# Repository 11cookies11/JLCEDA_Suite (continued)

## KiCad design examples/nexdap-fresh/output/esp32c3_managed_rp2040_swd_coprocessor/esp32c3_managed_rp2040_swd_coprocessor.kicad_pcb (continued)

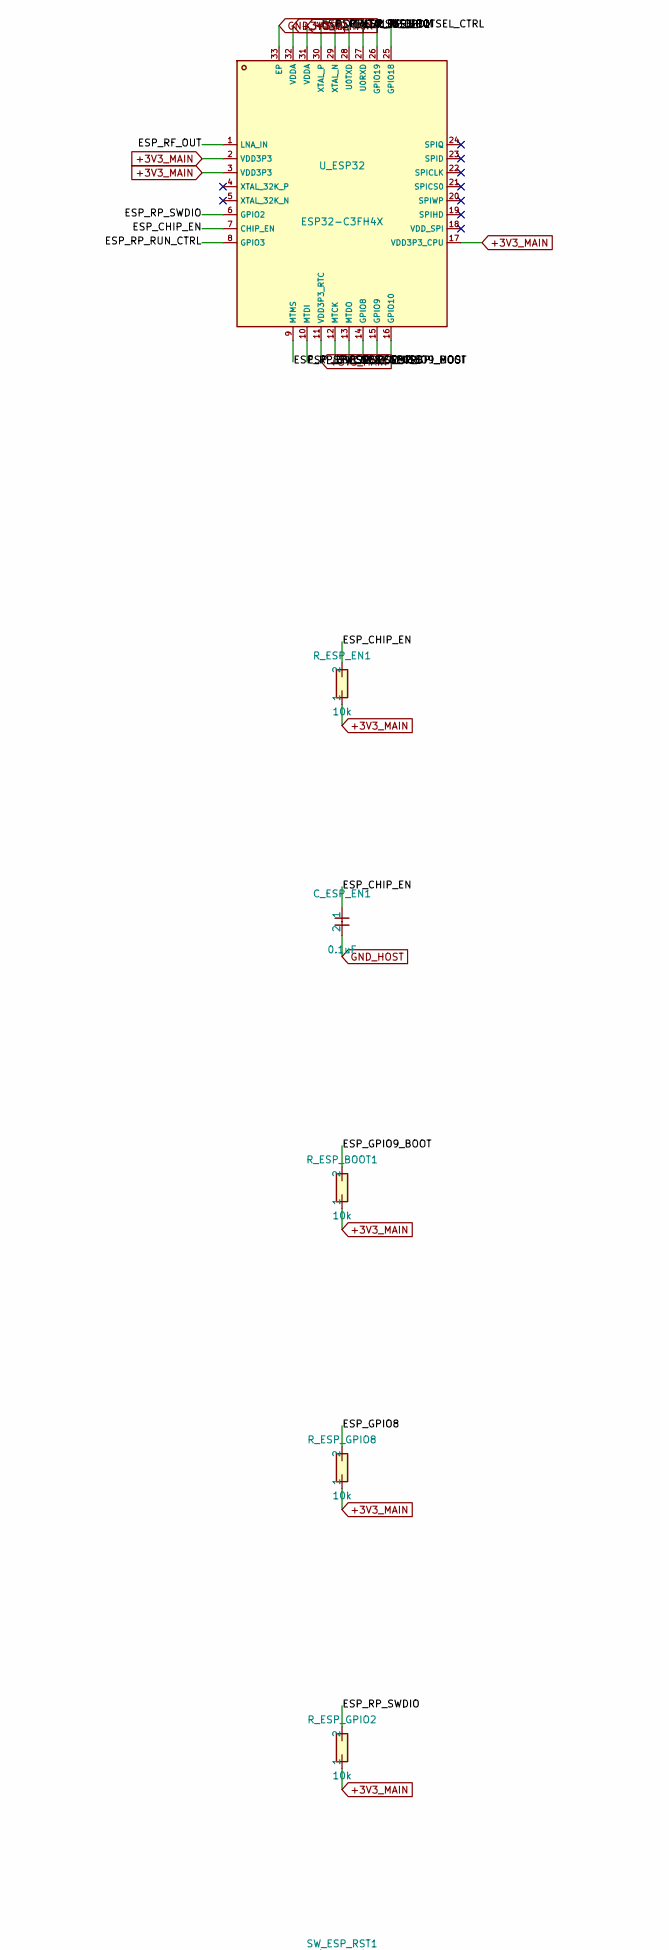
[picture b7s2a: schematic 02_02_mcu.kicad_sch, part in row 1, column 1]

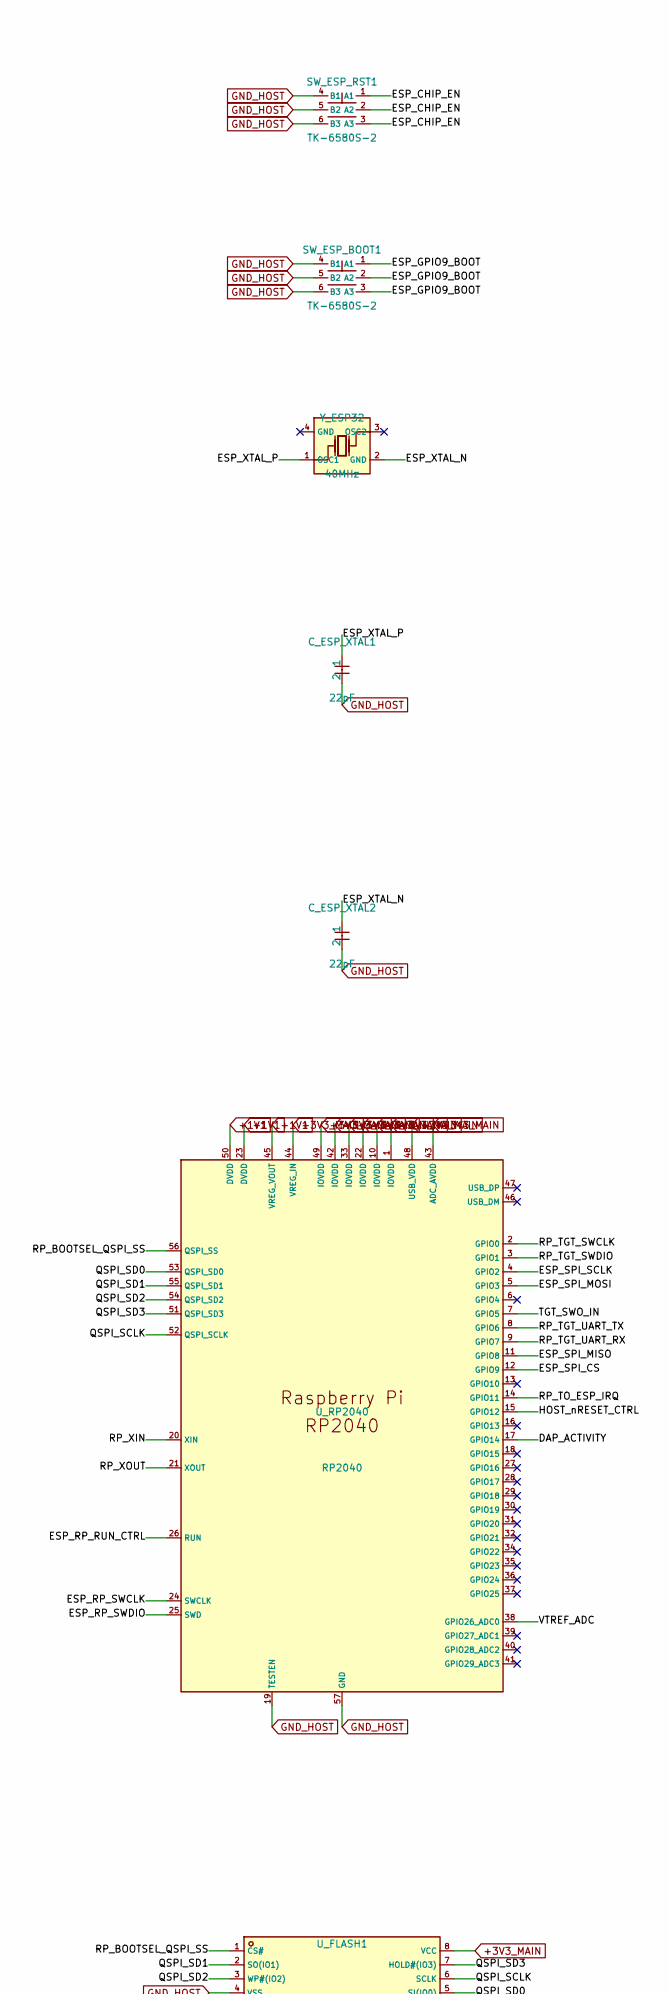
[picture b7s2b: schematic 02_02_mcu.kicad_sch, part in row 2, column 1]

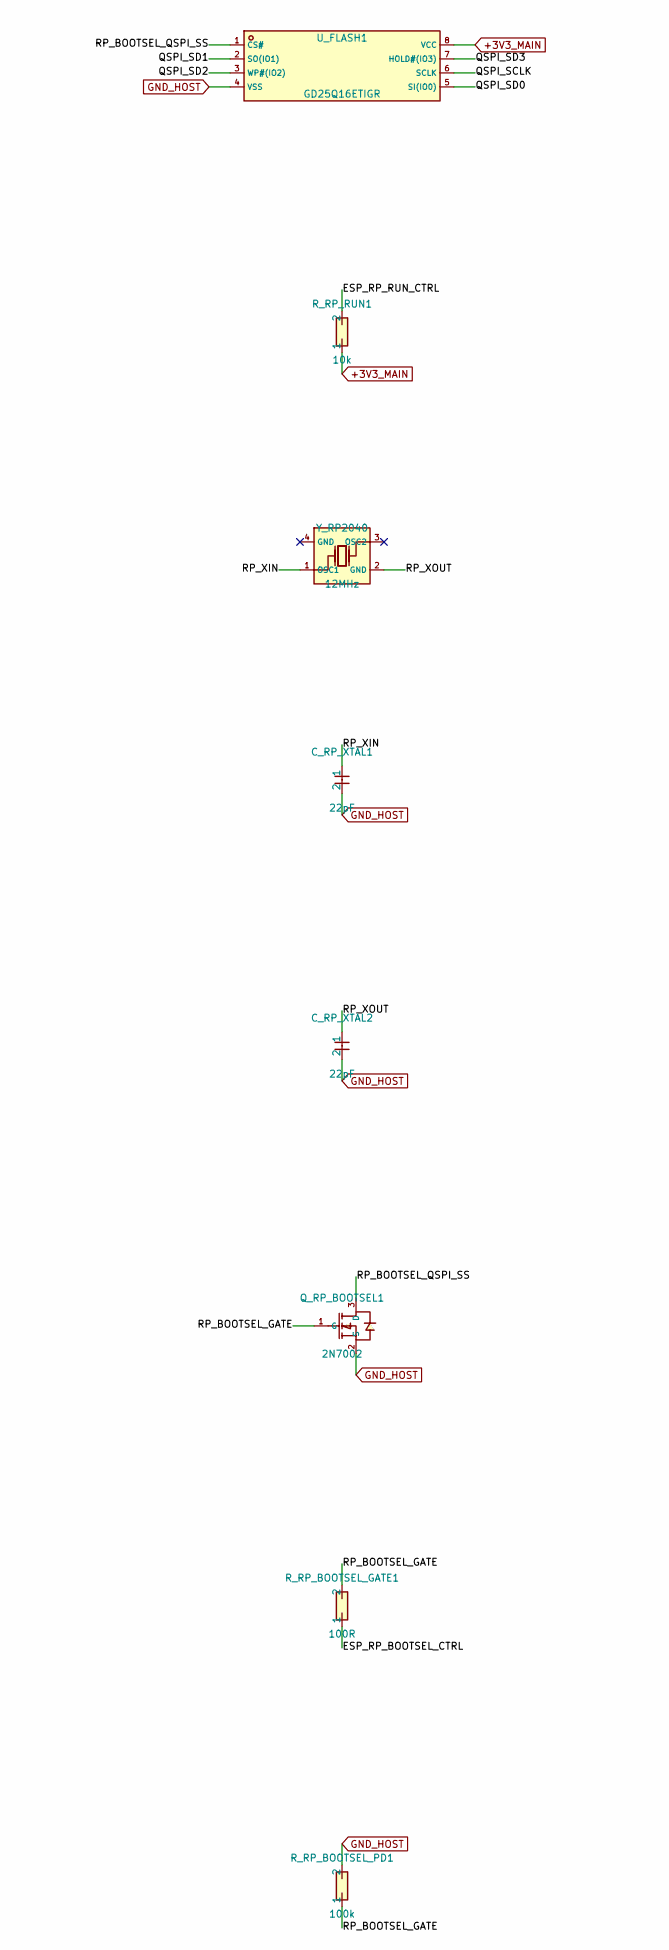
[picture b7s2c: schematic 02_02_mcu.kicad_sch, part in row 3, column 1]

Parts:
C_ESP_EN1: 0.1uF; C0603
C_ESP_XTAL1, C_ESP_XTAL2: 22pF; C0603
C_RP_XTAL1, C_RP_XTAL2: 22pF; C0603
Q_RP_BOOTSEL1: 2N7002; SOT-23-3_L2.9-W1.3-P1.90-LS2.4-BR
R_ESP_BOOT1: 10k; R0603
R_ESP_EN1: 10k; R0603
R_ESP_GPIO2, R_ESP_GPIO8: 10k; R0603
R_RP_BOOTSEL_GATE1: 100R; R0603
R_RP_BOOTSEL_PD1: 100k; R0603
R_RP_RUN1: 10k; R0603
SW_ESP_BOOT1: TK-6580S-2; SW-SMD_TK-6580S-2
SW_ESP_RST1: TK-6580S-2; SW-SMD_TK-6580S-2
U_ESP32: ESP32-C3FH4X; QFN-32_L5.0-W5.0-P0.50-TL-EP3.7
U_FLASH1: GD25Q16ETIGR; SOP-8_L4.9-W3.9-P1.27-LS6.0-BL
U_RP2040: RP2040; LQFN-56_L7.0-W7.0-P0.4-EP
Y_ESP32: 40MHz; CRYSTAL-SMD_4P-L3.2-W2.5-BL
Y_RP2040: 12MHz; CRYSTAL-SMD_4P-L3.2-W2.5-BL

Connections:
+1V1: U_RP2040.23 (DVDD), U_RP2040.45 (VREG_VOUT), U_RP2040.50 (DVDD); also elsewhere on the board
+3V3_MAIN: R_ESP_BOOT1.1, R_ESP_EN1.1, R_ESP_GPIO2.1, R_ESP_GPIO8.1, R_RP_RUN1.1, U_ESP32.2 (VDD3P3), U_ESP32.3 (VDD3P3), U_ESP32.11 (VDD3P3_RTC), U_ESP32.17 (VDD3P3_CPU), U_ESP32.31 (VDDA), U_ESP32.32 (VDDA), U_FLASH1.8 (VCC), U_RP2040.1 (IOVDD), U_RP2040.10 (IOVDD), U_RP2040.22 (IOVDD), U_RP2040.33 (IOVDD), U_RP2040.42 (IOVDD), U_RP2040.43 (ADC_AVDD), U_RP2040.44 (VREG_IN), U_RP2040.48 (USB_VDD), U_RP2040.49 (IOVDD); also elsewhere on the board
/02_mcu/DAP_ACTIVITY: U_RP2040.17 (GPIO14)
/02_mcu/ESP_CHIP_EN: C_ESP_EN1.1, R_ESP_EN1.2, SW_ESP_RST1.1 (A1), SW_ESP_RST1.2 (A2), SW_ESP_RST1.3 (A3), U_ESP32.7 (CHIP_EN)
/02_mcu/ESP_GPIO8: R_ESP_GPIO8.2, U_ESP32.14 (GPIO8)
/02_mcu/ESP_GPIO9_BOOT: R_ESP_BOOT1.2, SW_ESP_BOOT1.1 (A1), SW_ESP_BOOT1.2 (A2), SW_ESP_BOOT1.3 (A3), U_ESP32.15 (GPIO9)
/02_mcu/ESP_RF_OUT: U_ESP32.1 (LNA_IN)
/02_mcu/ESP_RP_BOOTSEL_CTRL: R_RP_BOOTSEL_GATE1.1, U_ESP32.27 (U0RXD)
/02_mcu/ESP_RP_RUN_CTRL: R_RP_RUN1.2, U_ESP32.8 (GPIO3), U_RP2040.26 (RUN)
/02_mcu/ESP_RP_SWCLK: U_ESP32.9 (MTMS), U_RP2040.24 (SWCLK)
/02_mcu/ESP_RP_SWDIO: R_ESP_GPIO2.2, U_ESP32.6 (GPIO2), U_RP2040.25 (SWD)
/02_mcu/ESP_SPI_CS: U_ESP32.12 (MTCK), U_RP2040.12 (GPIO9)
/02_mcu/ESP_SPI_MISO: U_ESP32.13 (MTDO), U_RP2040.11 (GPIO8)
/02_mcu/ESP_SPI_MOSI: U_ESP32.16 (GPIO10), U_RP2040.5 (GPIO3)
/02_mcu/ESP_SPI_SCLK: U_ESP32.10 (MTDI), U_RP2040.4 (GPIO2)
/02_mcu/ESP_XTAL_N: C_ESP_XTAL2.1, U_ESP32.29 (XTAL_N), Y_ESP32.2 (GND)
/02_mcu/ESP_XTAL_P: C_ESP_XTAL1.1, U_ESP32.30 (XTAL_P), Y_ESP32.1 (OSC1)
/02_mcu/HOST_nRESET_CTRL: U_RP2040.15 (GPIO12)
/02_mcu/QSPI_SCLK: U_FLASH1.6 (SCLK), U_RP2040.52 (QSPI_SCLK)
/02_mcu/QSPI_SD0: U_FLASH1.5 (SI(IO0)), U_RP2040.53 (QSPI_SD0)
/02_mcu/QSPI_SD1: U_FLASH1.2 (SO(IO1)), U_RP2040.55 (QSPI_SD1)
/02_mcu/QSPI_SD2: U_FLASH1.3 (WP#(IO2)), U_RP2040.54 (QSPI_SD2)
/02_mcu/QSPI_SD3: U_FLASH1.7 (HOLD#(IO3)), U_RP2040.51 (QSPI_SD3)
/02_mcu/RP_BOOTSEL_GATE: Q_RP_BOOTSEL1.1 (G), R_RP_BOOTSEL_GATE1.2, R_RP_BOOTSEL_PD1.1
/02_mcu/RP_BOOTSEL_QSPI_SS: Q_RP_BOOTSEL1.3 (D), U_FLASH1.1 (CS#), U_RP2040.56 (QSPI_SS)
/02_mcu/RP_TGT_SWCLK: U_RP2040.2 (GPIO0)
/02_mcu/RP_TGT_SWDIO: U_RP2040.3 (GPIO1)
/02_mcu/RP_TGT_UART_RX: U_RP2040.9 (GPIO7)
/02_mcu/RP_TGT_UART_TX: U_RP2040.8 (GPIO6)
/02_mcu/RP_TO_ESP_IRQ: U_ESP32.28 (U0TXD), U_RP2040.14 (GPIO11)
/02_mcu/RP_XIN: C_RP_XTAL1.1, U_RP2040.20 (XIN), Y_RP2040.1 (OSC1)
/02_mcu/RP_XOUT: C_RP_XTAL2.1, U_RP2040.21 (XOUT), Y_RP2040.2 (GND)
/02_mcu/TGT_SWO_IN: U_RP2040.7 (GPIO5)
/02_mcu/USB_DM: U_ESP32.25 (GPIO18)
/02_mcu/USB_DP: U_ESP32.26 (GPIO19)
/02_mcu/VTREF_ADC: U_RP2040.38 (GPIO26_ADC0)
GND_HOST: C_ESP_EN1.2, C_ESP_XTAL1.2, C_ESP_XTAL2.2, C_RP_XTAL1.2, C_RP_XTAL2.2, Q_RP_BOOTSEL1.2 (S), R_RP_BOOTSEL_PD1.2, SW_ESP_BOOT1.4 (B1), SW_ESP_BOOT1.5 (B2), SW_ESP_BOOT1.6 (B3), SW_ESP_RST1.4 (B1), SW_ESP_RST1.5 (B2), SW_ESP_RST1.6 (B3), U_ESP32.33 (EP), U_FLASH1.4 (VSS), U_RP2040.19 (TESTEN), U_RP2040.57 (GND); also elsewhere on the board

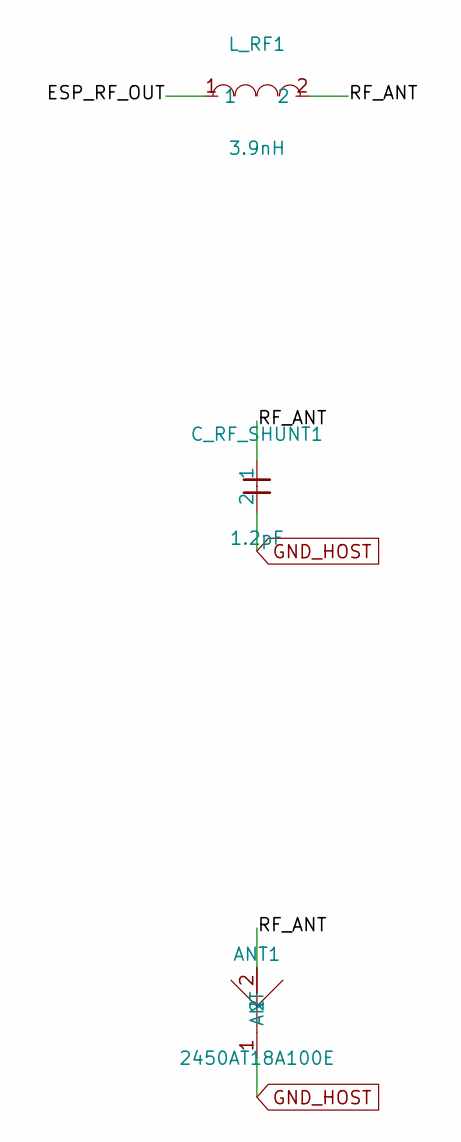
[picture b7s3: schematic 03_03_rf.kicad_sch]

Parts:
ANT1: 2450AT18A100E; ANT-SMD_L3.2-W1.6; MPN 2450AT18A100E; LCSC C89334
C_RF_SHUNT1: 1.2pF; C0603
L_RF1: 3.9nH; IND-SMD_L1.2-W0.7; MPN CS0402-3N9G-S; LCSC C285959

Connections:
/03_rf/ESP_RF_OUT: L_RF1.1
/03_rf/RF_ANT: ANT1.2, C_RF_SHUNT1.1, L_RF1.2
GND_HOST: ANT1.1 (ANT), C_RF_SHUNT1.2; also elsewhere on the board

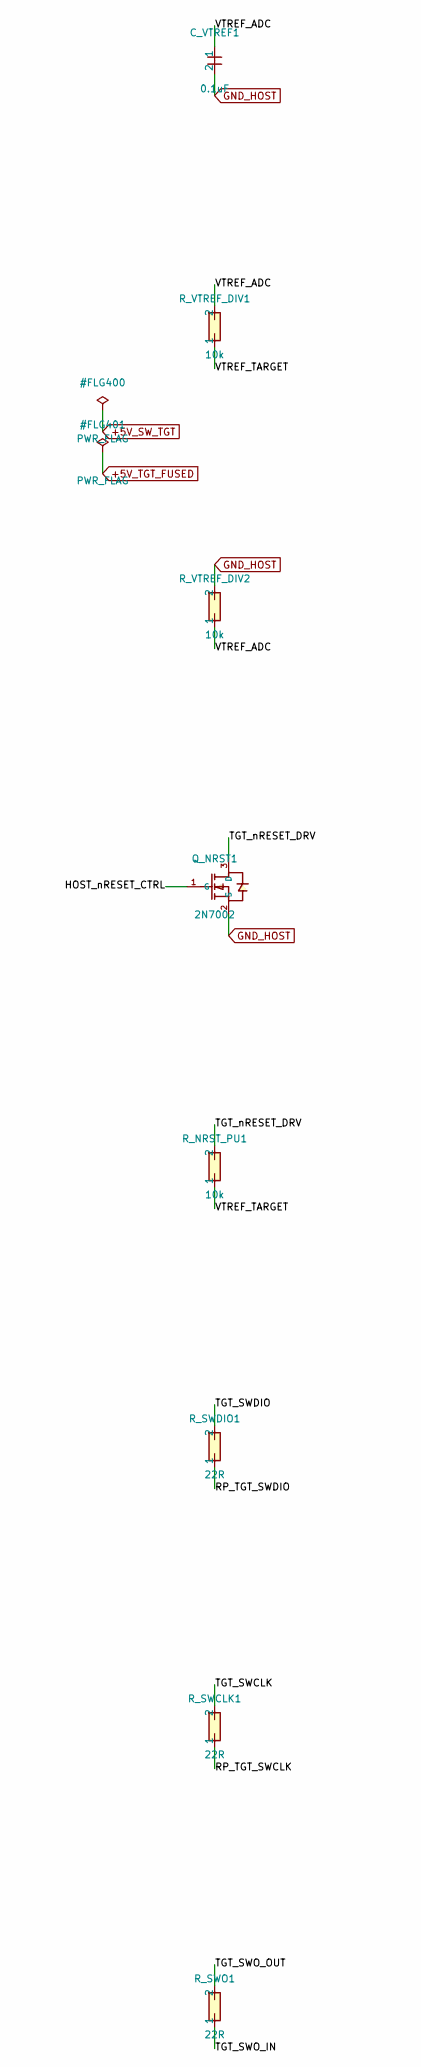
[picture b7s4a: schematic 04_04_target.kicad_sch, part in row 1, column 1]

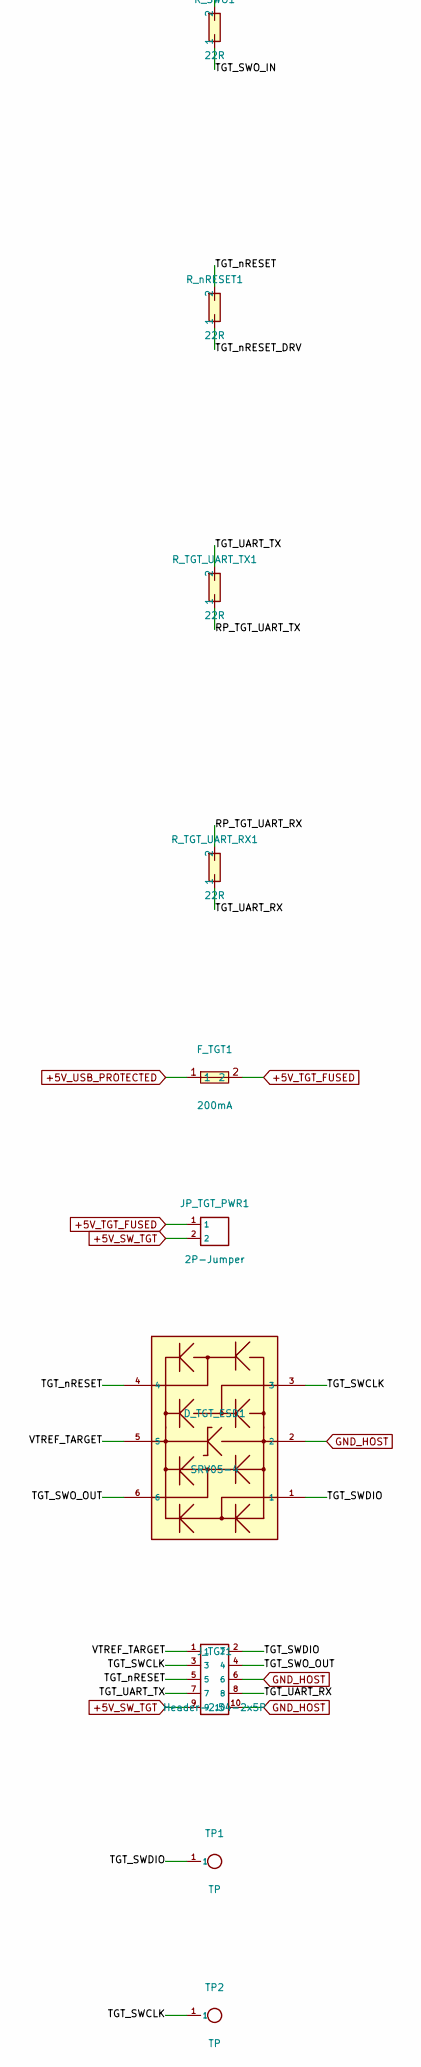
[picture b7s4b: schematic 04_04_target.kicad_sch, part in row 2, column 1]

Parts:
C_VTREF1: 0.1uF; C0603
D_TGT_ESD1: SRV05-4; SOT-23-6_L2.9-W1.6-P0.95-LS2.8-BL
F_TGT1: 200mA; F0805; MPN 0805L020/30XR; LCSC C7472560
JP_TGT_PWR1: 2P-Jumper; HDR-TH_2P-P2.54-V-M
J_TGT1: Header-2.54-2x5P; HDR-TH_10P-P2.54-V-M-2X5
Q_NRST1: 2N7002; SOT-23-3_L2.9-W1.3-P1.90-LS2.4-BR
R_NRST_PU1: 10k; R0603
R_SWCLK1: 22R; R0603
R_SWDIO1: 22R; R0603
R_SWO1: 22R; R0603
R_TGT_UART_RX1: 22R; R0603
R_TGT_UART_TX1: 22R; R0603
R_VTREF_DIV1, R_VTREF_DIV2: 10k; R0603
R_nRESET1: 22R; R0603
TP1, TP2: TP; TP-SMD_1P

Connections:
+5V_SW_TGT: JP_TGT_PWR1.2, J_TGT1.9; also elsewhere on the board
+5V_TGT_FUSED: F_TGT1.2, JP_TGT_PWR1.1
+5V_USB_PROTECTED: F_TGT1.1; also elsewhere on the board
/04_target/HOST_nRESET_CTRL: Q_NRST1.1 (G)
/04_target/RP_TGT_SWCLK: R_SWCLK1.1
/04_target/RP_TGT_SWDIO: R_SWDIO1.1
/04_target/RP_TGT_UART_RX: R_TGT_UART_RX1.2
/04_target/RP_TGT_UART_TX: R_TGT_UART_TX1.1
/04_target/TGT_SWCLK: D_TGT_ESD1.3, J_TGT1.3, R_SWCLK1.2, TP2.1 (1_1)
/04_target/TGT_SWDIO: D_TGT_ESD1.1, J_TGT1.2, R_SWDIO1.2, TP1.1 (1_1)
/04_target/TGT_SWO_IN: R_SWO1.1
/04_target/TGT_SWO_OUT: D_TGT_ESD1.6, J_TGT1.4, R_SWO1.2
/04_target/TGT_UART_RX: J_TGT1.8, R_TGT_UART_RX1.1
/04_target/TGT_UART_TX: J_TGT1.7, R_TGT_UART_TX1.2
/04_target/TGT_nRESET: D_TGT_ESD1.4, J_TGT1.5, R_nRESET1.2
/04_target/TGT_nRESET_DRV: Q_NRST1.3 (D), R_NRST_PU1.2, R_nRESET1.1
/04_target/VTREF_ADC: C_VTREF1.1, R_VTREF_DIV1.2, R_VTREF_DIV2.1
/04_target/VTREF_TARGET: D_TGT_ESD1.5, J_TGT1.1, R_NRST_PU1.1, R_VTREF_DIV1.1
GND_HOST: C_VTREF1.2, D_TGT_ESD1.2, J_TGT1.6, J_TGT1.10, Q_NRST1.2 (S), R_VTREF_DIV2.2; also elsewhere on the board

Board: 2 copper layers, 68 parts (0 on the bottom side), 49 nets, no tracks yet.

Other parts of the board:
LED_DAP1: Blue; LED0603-RD
LED_PWR1: Green; LED0603-RD
LED_TGT1: Red; LED0603-RD
R_LED_DAP1: 330R; R0603
R_LED_PWR1: 330R; R0603
R_LED_TGT1: 330R; R0603

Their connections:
+3V3_MAIN: R_LED_DAP1.1, R_LED_PWR1.1; also elsewhere on the board
+5V_SW_TGT: R_LED_TGT1.1; also elsewhere on the board
/05_indicator/LED_DAP_A: LED_DAP1.2 (+), R_LED_DAP1.2
/05_indicator/LED_PWR_A: LED_PWR1.2 (+), R_LED_PWR1.2
/05_indicator/LED_TGT_K: LED_TGT1.2 (+), R_LED_TGT1.2
GND_HOST: LED_PWR1.1 (-), LED_TGT1.1 (-); also elsewhere on the board

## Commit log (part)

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2026-04-07 docs(repo): define JLCEDA AIAgent foundation
    English summary:
    - replace template README content with project-specific positioning
    - add Where planning files and repository agent guidance
    中文摘要：
    - 将模板 README 替换为项目专用说明
    - 增加 Where 规划文件与仓库级代理约定
2026-04-07 chore(deps): bump amannn/action-semantic-pull-request from 5 to 6
    Bumps [amannn/action-semantic-pull-request](https://github.com/amannn/action-semantic-pull-request) from 5 to 6.
    - [Release notes](https://github.com/amannn/action-semantic-pull-request/releases)
    - [Changelog](https://github.com/amannn/action-semantic-pull-request/blob/main/CHANGELOG.md)
    - [Commits](https://github.com/amannn/action-semantic-pull-request/compare/v5...v6)
    ---
    updated-dependencies:
2026-04-07 feat(export): add project BOM export flow
    English summary:
    - add project BOM export support through the schematic manufacture-data API
    - complete the first hardware workflow path with export metadata returned by the bridge
    中文摘要：
    - 基于原理图生产资料 API 增加工程 BOM 导出能力
    - 通过桥接层返回导出元数据，补齐首个硬件工作流闭环
2026-04-07 ﻿docs(status): align docs with current bridge progress
    English summary:
    - refresh readmes, plan notes, and changelogs to reflect the implemented bridge workflow
    - document the current validation path and the remaining JLCEDA runtime verification gap
    中文摘要：
    - 同步 README、计划说明和更新日志，使其与当前桥接实现进度保持一致
    - 明确当前验证路径以及仍待完成的 JLCEDA 实机验证缺口
2026-04-07 ﻿feat(server): add bridge websocket service skeleton
    English summary:
    - add a minimal bridge server with websocket session registration, heartbeats, request routing, and a server smoke test
    - update project docs and release checks to include the new server-side validation path
    中文摘要：
    - 增加最小可用的桥接服务端，支持 WebSocket 会话注册、心跳、请求路由和服务端冒烟测试
    - 同步项目文档和发布校验流程，纳入新的服务端验证路径
2026-04-07 ﻿refactor(ui): simplify bridge menu presentation
    English summary:
    - reduce the top-level bridge menu to a smaller set of actions and move secondary tasks into a quick-action picker
    - replace raw json-style status dialogs with clearer sectioned summaries in Chinese
    中文摘要：
    - 精简顶部桥接菜单，把次级操作收进快捷选择入口
    - 将原始 JSON 风格状态弹窗改为更清晰的中文分段摘要
2026-04-07 ﻿fix(ui): timeout custom popup initialization
    English summary:
    - add a timeout around the custom bridge dialog initialization so the plugin can fall back instead of hanging silently
    - keep the simplified popup path reachable while we investigate a more reliable advanced dialog approach
    中文摘要：
    - 为自定义桥接弹窗初始化增加超时控制，避免界面静默卡住
    - 在继续排查高级弹窗方案时，确保简化弹窗路径仍然可用
2026-04-07 ﻿feat(ui): wire iframe actions to plugin bridge
    English summary:
    - connect the iframe bridge window to plugin-side capabilities through the message bus so status, document, diagnostics, and remote settings can run inside the popup
    - keep bridge results inside the same window instead of bouncing users back to native selection dialogs
    中文摘要：
    - 通过消息总线把 iframe 桥接窗口接到插件侧能力上，让状态、文档、诊断和远程配置都能在窗口内执行
    - 将桥接结果留在同一个窗口内展示，避免再跳回原生系统选择框
2026-04-07 fix(menu): rotate bridge menu ids to flush stale entries
    - bump the plugin package version to 0.1.2 for a clean JLCEDA reload
    - rotate header menu and menu item ids across home, schematic, and pcb contexts to avoid stale cached menu entries
    - update the iframe footer version so runtime verification matches the packaged build
2026-04-08 stabilize bridge ui rpc
2026-04-08 chore: checkpoint current bridge state
    English summary:
    - Capture the current JLCEDA bridge implementation as a clean baseline before expanding API coverage.
    - No source files changed in this checkpoint; the repository state is already committed and verified.
    中文摘要：
    - 将当前 JLCEDA 桥接实现作为一个干净基线保存，便于后续继续扩展 API 覆盖面。
    - 此次检查点未修改源码；当前仓库状态已是干净且可验证的。
2026-04-08 feat(bridge): add callback registration commands
    Add shortcut, timer, and right-click callback bridge commands.
    补齐快捷键、定时器和右键菜单回调注册命令，并增加回调事件队列检查与文档说明。
2026-04-08 feat(bridge): add generic api invoke path
2026-04-08 chore(release): bump plugin to 0.1.10
2026-04-08 fix(remote): add connection timeout watchdog
2026-04-08 feat(update): support private github releases
2026-04-09 fix(pcb): add footprint source fallback
2026-04-09 feat: move bridge server to python
2026-04-09 fix(schematic): avoid overlapping component placement
2026-04-09 feat: add server rule profiles
2026-04-09 feat: profile schematic placement clearances
2026-04-09 release: v0.1.21
2026-04-09 fix(metadata): restore extension detail content for packaging
    English summary:
    - include README files in the packaged extension so extension managers can render detail content
    - add homepage and issue tracker links to the extension manifest metadata
    - bump the suite version to 0.1.23 and document the packaging fix in the changelog
    ?????
    - ? README ??????????????????????????
2026-04-10 feat(skill): add schematic context intake flow
    English summary:
    - add a server context summary script that collects bridge status, document summary, selection snapshot, and current schematic context
    - add a smoke test and package scripts for the new context-summary workflow
    - reshape the jlceda-suite-skill docs around inspect/select/design/export modes for schematic-first collaboration
    中文摘要:
    - 增加 server context summary 脚本，用于汇总 bridge 状态、文档摘要、选择快照和当前原理图上下文
2026-04-11 feat(skill): add pcb assistance workflow
    English summary:
    - add a pcb-assist workflow that reads schematic and pcb context, inspects layout hygiene, and outputs placement advice plus next tasks
    - add a smoke test, skill entrypoint, and pcb assistance reference documentation
    - update package scripts and sync the where plan progress for schematic-first collaboration
    中文摘要:
    - 新增 PCB 辅助工作流，读取原理图与 PCB 上下文，检查布局卫生，并输出布局建议与后续任务
2026-04-11 feat(skill): require verified pin metadata in selection
2026-04-12 feat(release): ship v0.1.27 placement validation and plan compiler
    English summary:
    - add Python multipage placement validation workflow for fen-P test demos
    - add circuit-model to execution-plan compiler and schema/docs updates
    - fix placement collision avoidance with runtime occupancy check
2026-04-16 feat(server): add strict SCD pipeline
    English summary:\n- Add a strict Schematic Construction Description (SCD) layer to the text-to-schematic pipeline.\n- Generate readable schematic construction output, validate it with a parser, and w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
2026-04-19 feat(simulation): add spice netlist exporter
    English summary:
    - add a spice-netlist.v1 schema and a SpiceNetlist model in the text-to-schematic pipeline
    - export a simulation-ready SPICE text file plus JSON metadata alongside netlist.json
    - keep unsupported components explicit as warnings/comments instead of silently guessing active devices
    中文摘要：
    - 新增 spice-netlist.v1 schema 和 SpiceNetlist 导出层
2026-04-19 feat(simulation): add ngspice regression runner
2026-05-14 chore(repo): clean active hardware workflow layout
    中文：清理仓库根目录和当前 skill，将旧 EasyEDA/JLCEDA 插件资源与 live-bridge skill 文件归档到 legacy，并把模型契约从 server/schemas 迁移到 schemas。
    English: Clean the repository root and active skill by archiving legacy EasyEDA/JLCEDA plugin resources and live-bridge skill files under legacy, and move model contracts from server/schemas to schem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
    中文：保留当前 KiCad/硬件开发主线所需的 schema、配置和 reference，同时更新 README/docs 路径引用。
    English: Keep the schemas, configs, and references needed by the active KiCad hardware-development workflow while updating READM
2026-05-15 chore: ignore generated where outputs
    English summary:
    - Ignore local .where demo and generated output directories.
    - Remove the current untracked generated outputs from the working tree.
    中文摘要：
    - 忽略本地 .where demo 和生成输出目录。
    - 清理当前工作区中未跟踪的生成产物。
2026-05-15 refactor(tooling): surface structured fallback warnings
    中文说明：\n- 将 parts / adapter / validation / pipeline 分层进一步收紧\n- 让 summary 顶层 warnings 可见，并由 validate-artifacts 的 strict 模式拦截\n- 补齐适配器、流水线、中间层和验证层测试\n- 同步更新 README 与 skill，说明回退路径需要复核
2026-05-16 refactor(tooling): tighten schema contracts and fixture coverage
    English: add canonical schema constants and field-level contracts, expand compatibility and failure fixtures, and keep wrapper retirement guidance aligned across docs and skill notes.
    中文：补充统一的 schema 常量和字段级契约，扩展兼容与失败场景的 fixture 与回归测试，并同步收紧文档与 skill 中的包装器退场说明。
2026-05-18 Update NexDAP example outputs and fix KiCad mapping logic / 更新 NexDAP 示例输出并修正 KiCad 映射逻辑
2026-05-18 Add time-based pipeline event logging / 增加按时间记录的流水线日志
2026-05-26 feat(h618): consolidate schematic sheets / 整理原理图分页
    将 H618 KiCad 原理图从大量小分图整理为 8 个可评审模块页，补充分图 profile 和回归测试，并同步 H618 文档、模型、example 工程与 where 进度。
    Consolidate the H618 KiCad schematic into eight reviewable module sheets, add sheet grouping coverage, and sync the H618 model, docs, generated example project, and where progress.
2026-05-27 fix(project-state): align API dry-run and IR export semantics 修正 API dry-run 与 IR 导出语义
    - Prevent model-api dry-run, validate-only, and no-commit requests from mutating project.state.json
    - Route model-api export_kicad_project through build_ir -> ir_to_kicad -> write_project
    - Fix power_rail_count summary and narrow build-operation classification
    - Add Claude Code project state management design note and regression tests
    - 防止 model-api dry-run、validate-only、no-commit 请求污染 project.state.json
    - 将 model-api export_kicad_project 统一切到 build_ir -> ir_to_kicad -> write_project
2026-05-29 chore: remove .history, lock file and backups from tracking 清理临时文件
2026-06-03 Fix JLC footprint and symbol resolution
2026-06-04 chore: ignore generated artifacts / 忽略生成产物
2026-06-04 test: align regression suite with new package layout / 测试：对齐新包结构的回归套件
2026-06-04 refactor: remove symbol fallback paths / 重构：移除符号兜底路径
2026-06-04 release: bump to 0.3.2 / 发布：升级到 0.3.2
2026-06-06 refactor(jlc): centralize EasyEDA access policy
    English summary:
    - Introduce a shared EasyEDAAccessPolicy for resolve-symbols retries, pacing, and 403 cooldown handling.
    - Remove redundant delay plumbing from resolve-symbols CLI/service boundaries and clean up the legacy import script interface.
    - Keep batch import and PCB generation changes aligned with the new retry/pacing behavior.
    中文摘要：
    - 为 resolve-symbols 引入统一的 EasyEDAAccessPolicy，集中管理随机等待、403 冷却和重试次数。
2026-06-09 fix(orchestration): route missing selections before library failures
    English summary:\n- Split library resolution routing so components missing LCSC selection are sent to lcsc_selection_v1 before download failures are turned into repair tasks.\n\n中文摘要：\n- 将缺少 LCSC 选型的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
2026-06-15 fix(kicad): strip broken 3d model refs
    English summary:\n- Rewrite project-local 3D references when a matching asset exists.\n- Remove unresolved 3D model blocks so KiCad viewers do not keep broken links.\n- Keep the example project self-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
2026-06-15 feat(kicad): hook design intent gate into project creation / 将设计意图门禁接入创建流程
2026-06-20 feat(example): revise AI badge module design
    English summary:
    - Replace the bare ESP32 design with the Rev A ESP32-S3-WROOM module architecture.
    - Add the power-path, display, NFC, audio, storage, and UI refinements with selected LCSC parts.
    - Document the BOM, pin assignment, layout constraints, risks, and design changes.
    中文摘要：
    - 将裸 ESP32 方案更新为 Rev A ESP32-S3-WROOM 模块架构。
2026-06-20 fix(kicad): expose footprint metadata for import
    English summary:
    - Keep KiCad footprint properties visible to downstream importers.
    - Render the metadata at a negligible size to preserve schematic readability.
    中文摘要：
    - 使下游导入器可读取 KiCad 封装属性。
    - 使用极小字体保留元数据，同时不影响原理图可读性。
2026-06-20 feat(hardware): add hardware ERC schema
2026-06-20 docs(hardware): add hardware design agent prompt
2026-06-20 ci: upload pytest log for debugging
2026-06-24 fix(hardware): enforce semantic gate before KiCad export
    English summary:\n- Run the hardware semantic gate before agent KiCad export and block export when the gate reports blockers.\n- Tighten load-switch VOUT checks so capacitors, resistors, and test poi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
